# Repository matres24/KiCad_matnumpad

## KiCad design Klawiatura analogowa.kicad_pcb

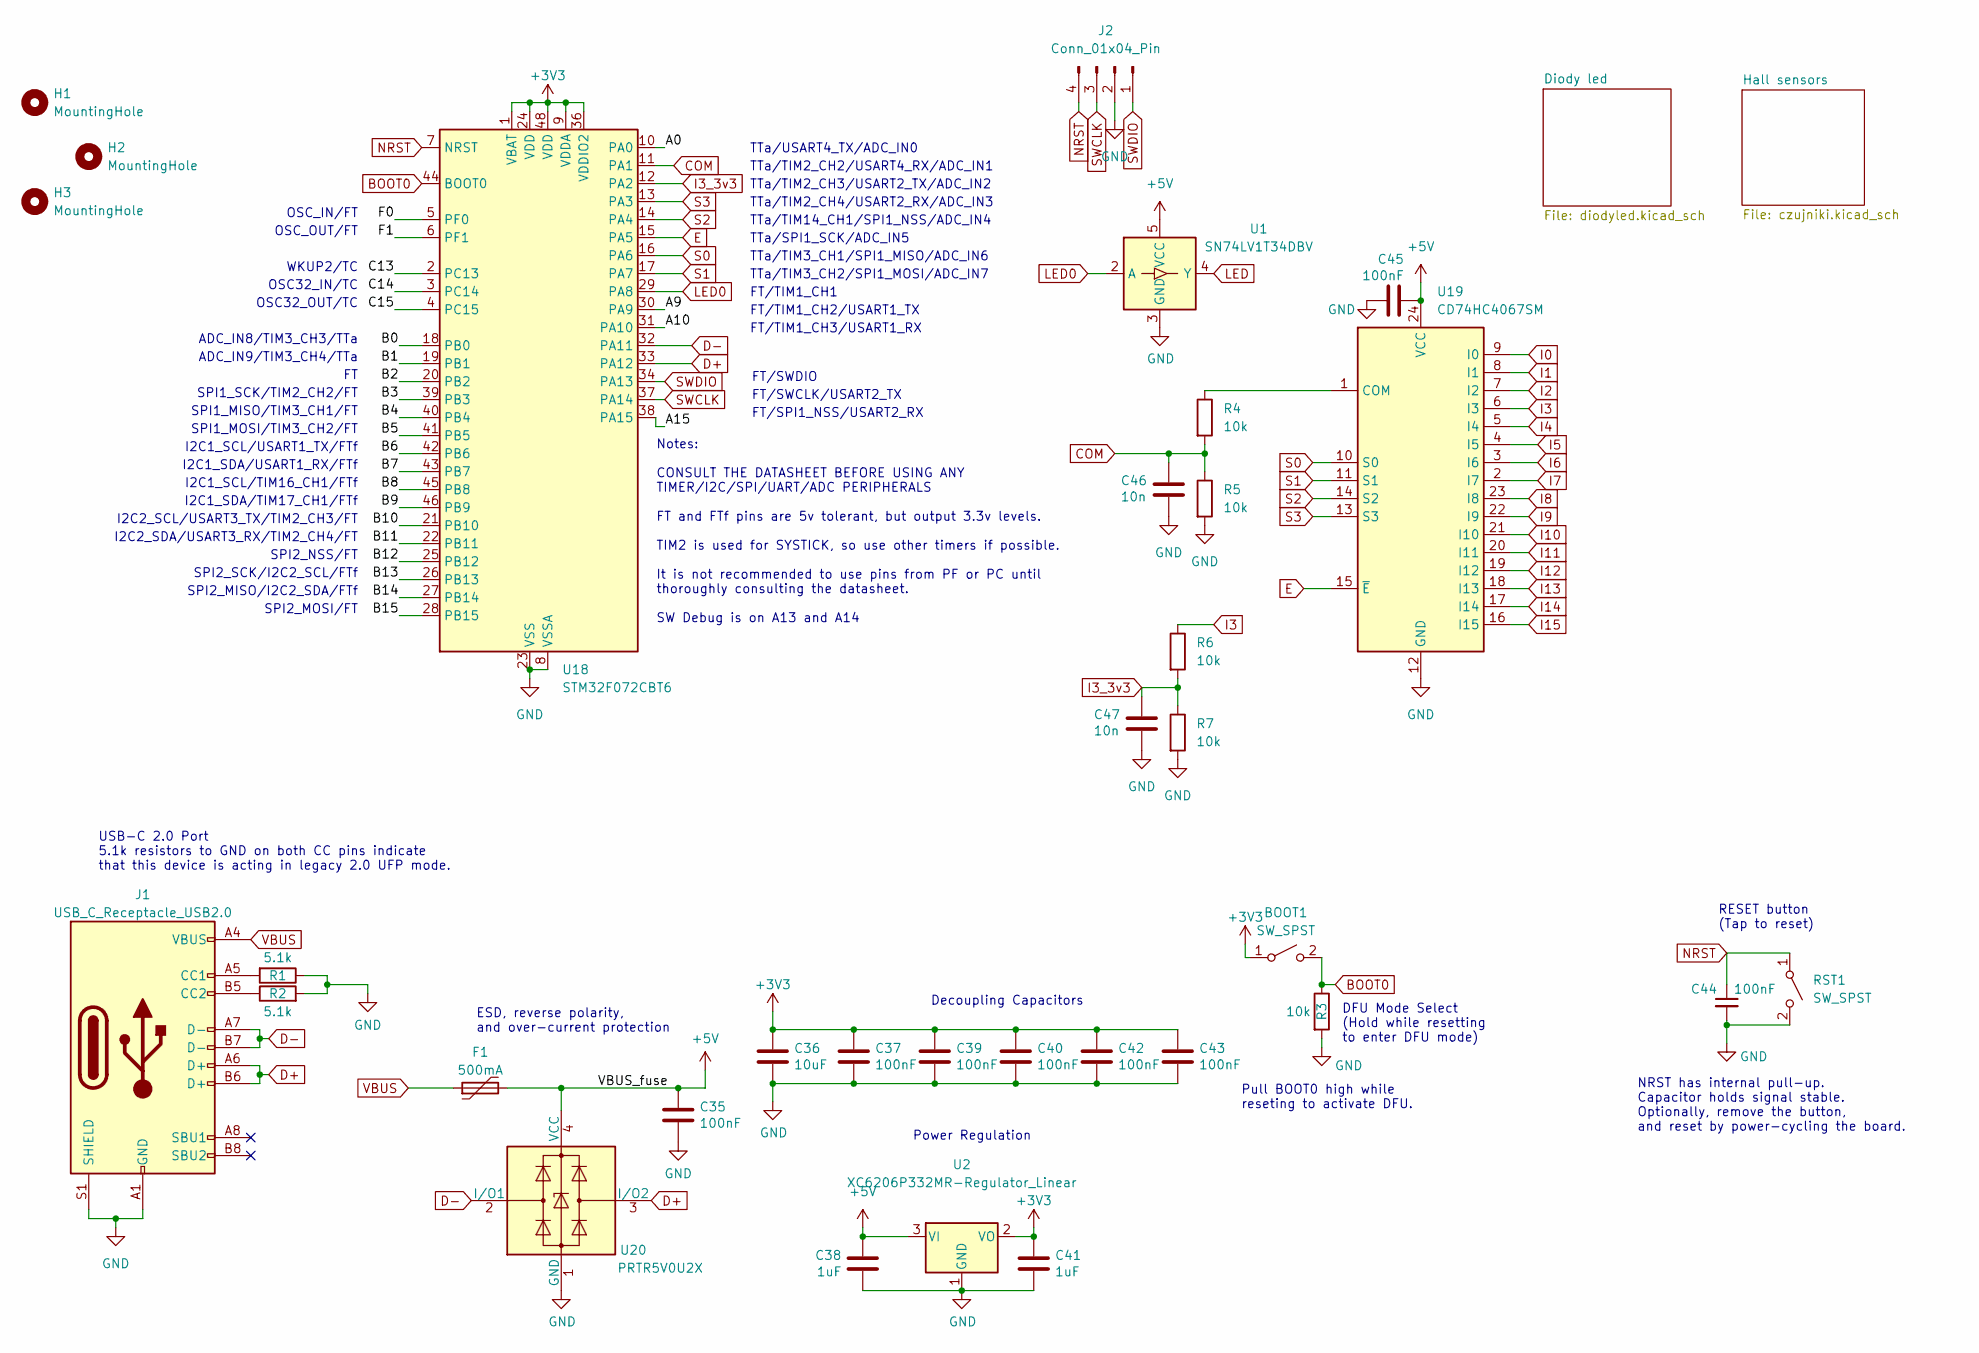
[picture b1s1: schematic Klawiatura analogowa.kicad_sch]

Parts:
BOOT1: SW_SPST; SW_SPST_B3U-1000P
C35, C37, C39, C40, C42, C43, C44, C45: 100nF; C_0402_1005Metric; LCSC C307331
C36: 10uF; C_0603_1608Metric; LCSC C307331
C38, C41: 1uF; C_0402_1005Metric; LCSC C307331
C46, C47: 10n; C_0402_1005Metric
F1: 500mA; Fuse_1206_3216Metric; LCSC C135341
H1, H2, H3: MountingHole; MountingHole_2.2mm_M2_ISO7380_Pad
J1: USB_C_Receptacle_USB2.0; USB_C_Receptacle_HRO_TYPE-C-31-M-12; JlcRotOffset 180
J2: Conn_01x04_Pin; PinHeader_1x04_P1.27mm_Vertical
R1, R2: 5.1k; R_0402_1005Metric
R3, R4, R5, R6, R7: 10k; R_0402_1005Metric
RST1: SW_SPST; SW_SPST_B3U-1000P
U1: SN74LV1T34DBV; SOT-23-5
U2: XC6206P332MR-Regulator_Linear; SOT-23; LCSC C5446
U18: STM32F072CBT6; LQFP-48_7x7mm_P0.5mm; JlcRotOffset 90
U19: CD74HC4067SM; SSOP-24_5.3x8.2mm_P0.65mm
U20: PRTR5V0U2X; SOT-143; LCSC C2827688

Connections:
+3V3: BOOT1.1 (A), C36.1, C37.1, C39.1, C40.1, C41.1, C42.1, C43.1, U2.2 (VO), U18.1 (VBAT), U18.9 (VDDA), U18.24 (VDD), U18.36 (VDDIO2), U18.48 (VDD)
+5V: C35.1, C38.1, C45.2, F1.2, U1.5 (VCC), U2.3 (VI), U19.24 (VCC), U20.4 (VCC); also elsewhere on the board
/A0: U18.10 (PA0)
/A9: U18.30 (PA9)
/A10: U18.31 (PA10)
/A15: U18.38 (PA15)
/B0: U18.18 (PB0)
/B1: U18.19 (PB1)
/B2: U18.20 (PB2)
/B3: U18.39 (PB3)
/B4: U18.40 (PB4)
/B5: U18.41 (PB5)
/B6: U18.42 (PB6)
/B7: U18.43 (PB7)
/B8: U18.45 (PB8)
/B9: U18.46 (PB9)
/B10: U18.21 (PB10)
/B11: U18.22 (PB11)
/B12: U18.25 (PB12)
/B13: U18.26 (PB13)
/B14: U18.27 (PB14)
/B15: U18.28 (PB15)
/C13: U18.2 (PC13)
/C14: U18.3 (PC14)
/C15: U18.4 (PC15)
/F0: U18.5 (PF0)
/F1: U18.6 (PF1)
BOOT0: BOOT1.2 (B), R3.1, U18.44 (BOOT0)
COM: C46.1, R4.2, R5.1, U18.11 (PA1)
D+: J1.A6 (D+), J1.B6 (D+), U18.33 (PA12), U20.3 (I/O2)
D-: J1.A7 (D-), J1.B7 (D-), U18.32 (PA11), U20.2 (I/O1)
E: U18.15 (PA5), U19.15 (~E)
GND: C35.2, C36.2, C37.2, C38.2, C39.2, C40.2, C41.2, C42.2, C43.2, C44.2, C45.1, C46.2, C47.2, J1.A1 (GND), J1.A12 (GND), J1.B1 (GND), J1.B12 (GND), J1.S1 (SHIELD), J2.2, R1.1, R2.2, R3.2, R5.2, R7.2, RST1.2 (B), U1.3 (GND), U2.1 (GND), U18.8 (VSSA), U18.23 (VSS), U18.35 (VSS), U18.47 (VSS), U19.12 (GND), U20.1 (GND); also elsewhere on the board
I0: U19.9 (I0); also elsewhere on the board
I1: U19.8 (I1); also elsewhere on the board
I2: U19.7 (I2); also elsewhere on the board
I3: R6.1, U19.6 (I3); also elsewhere on the board
I3_3v3: C47.1, R6.2, R7.1, U18.12 (PA2)
I4: U19.5 (I4); also elsewhere on the board
I5: U19.4 (I5); also elsewhere on the board
I6: U19.3 (I6); also elsewhere on the board
I7: U19.2 (I7); also elsewhere on the board
I8: U19.23 (I8); also elsewhere on the board
I9: U19.22 (I9); also elsewhere on the board
I10: U19.21 (I10); also elsewhere on the board
I11: U19.20 (I11); also elsewhere on the board
I12: U19.19 (I12); also elsewhere on the board
I13: U19.18 (I13); also elsewhere on the board
I14: U19.17 (I14); also elsewhere on the board
I15: U19.16 (I15); also elsewhere on the board
LED: U1.4 (Y); also elsewhere on the board
LED0: U1.2 (A), U18.29 (PA8)
NRST: C44.1, J2.4, RST1.1 (A), U18.7 (NRST)
unnamed: J1.A5 (CC1), R1.2
unnamed: J1.B5 (CC2), R2.1
unnamed: R4.1, U19.1 (COM)
S0: U18.16 (PA6), U19.10 (S0)
S1: U18.17 (PA7), U19.11 (S1)
S2: U18.14 (PA4), U19.14 (S2)
S3: U18.13 (PA3), U19.13 (S3)
SWCLK: J2.3, U18.37 (PA14)
SWDIO: J2.1, U18.34 (PA13)
VBUS: F1.1, J1.A4 (VBUS), J1.A9 (VBUS), J1.B4 (VBUS), J1.B9 (VBUS)

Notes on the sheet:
SPI1_MISO/TIM3_CH1/FT
SPI2_MISO/I2C2_SDA/FTf
Notes: CONSULT THE DATASHEET BEFORE USING ANY TIMER/I2C/SPI/UART/ADC PERIPHERALS FT and FTf pins are 5v tolerant, but output 3.3v levels. TIM2 is used for SYSTICK, so use other timers if possible. It is not recommended to use pins from PF or PC until thoroughly consulting the datasheet. SW Debug is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
I2C2_SDA/USART3_RX/TIM2_CH4/FT
ESD, reverse polarity, and over-current protection
I2C1_SDA/USART1_RX/FTf
OSC_OUT/FT
USB-C 2.0 Port 5.1k resistors to GND on both CC pins indicate that this device is acting in legacy 2.0 UFP mode.
DFU Mode Select (Hold while resetting to enter DFU mode)
FT/SWDIO
TTa/TIM3_CH1/SPI1_MISO/ADC_IN6
TTa/SPI1_SCK/ADC_IN5
TTa/TIM2_CH3/USART2_TX/ADC_IN2
TTa/TIM3_CH2/SPI1_MOSI/ADC_IN7
SPI2_SCK/I2C2_SCL/FTf
ADC_IN8/TIM3_CH3/TTa
ADC_IN9/TIM3_CH4/TTa
OSC32_OUT/TC
SPI2_NSS/FT
Power Regulation
I2C2_SCL/USART3_TX/TIM2_CH3/FT
SPI2_MOSI/FT
RESET button (Tap to reset)
TTa/TIM14_CH1/SPI1_NSS/ADC_IN4
FT/TIM1_CH1
I2C1_SDA/TIM17_CH1/FTf
SPI1_MOSI/TIM3_CH2/FT
TTa/TIM2_CH4/USART2_RX/ADC_IN3
I2C1_SCL/TIM16_CH1/FTf
OSC32_IN/TC
WKUP2/TC
FT/TIM1_CH3/USART1_RX
NRST has internal pull-up. Capacitor holds signal stable. Optionally, remove the button, and reset by power-cycling the board.
FT/SPI1_NSS/USART2_RX
I2C1_SCL/USART1_TX/FTf
FT/SWCLK/USART2_TX
OSC_IN/FT
Pull BOOT0 high while reseting to activate DFU.
Decoupling Capacitors
TTa/USART4_TX/ADC_IN0

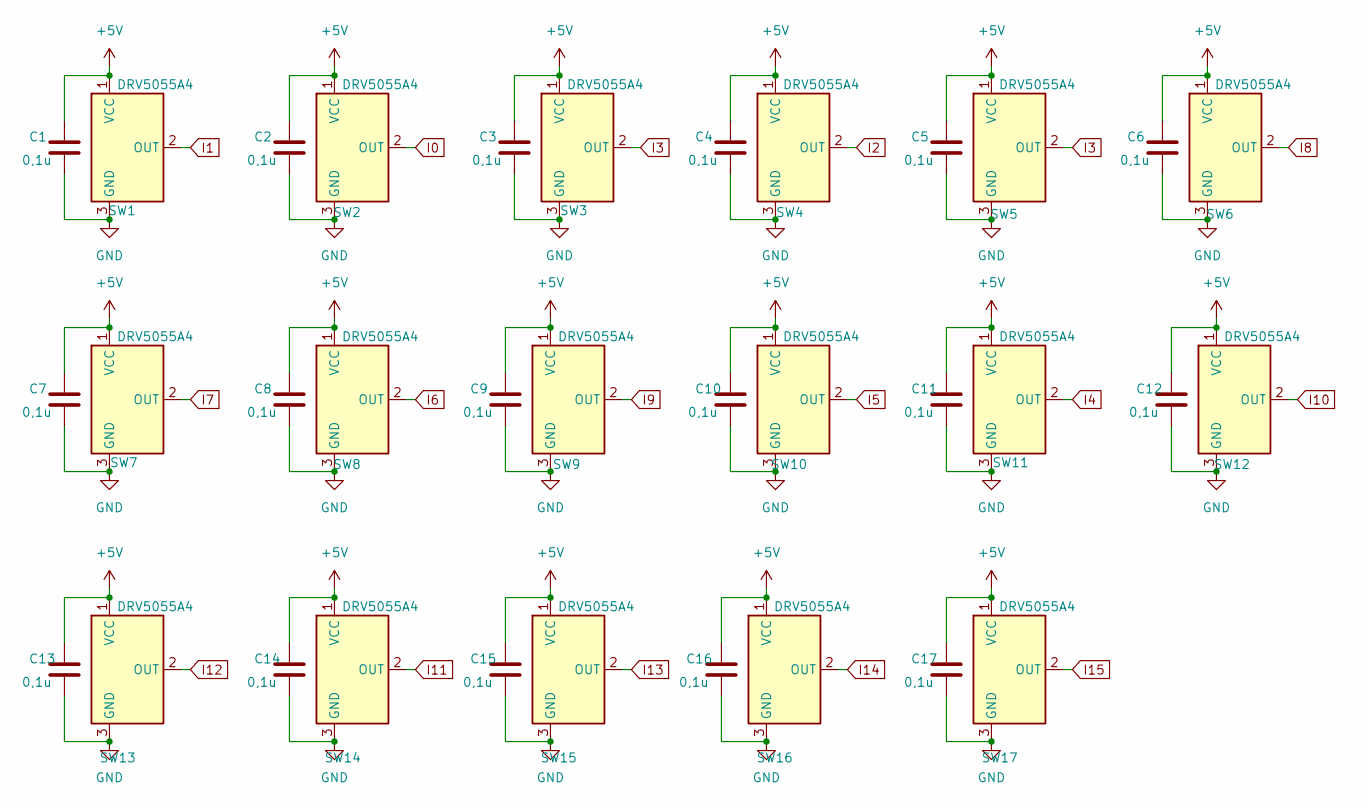
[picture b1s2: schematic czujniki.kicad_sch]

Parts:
C1, C2, C3, C4, C5, C6, C7, C8, C9, C10, C11, C12, C13, C14, C15, C16, C17: 0,1u; C_0402_1005Metric
SW1, SW2, SW3, SW4, SW5, SW6, SW7, SW8, SW9, SW10, SW11, SW12, SW14, SW17: DRV5055A4; MX-Analog-1U
SW13: DRV5055A4; MX-Analog-2U
SW15, SW16: DRV5055A4; MX-Analog-2U-Vertical-ReversedStabilizers

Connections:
+5V: C1.1, C2.1, C3.1, C4.1, C5.1, C6.1, C7.1, C8.1, C9.1, C10.1, C11.1, C12.1, C13.1, C14.1, C15.1, C16.1, C17.1, SW1.1 (VCC), SW2.1 (VCC), SW3.1 (VCC), SW4.1 (VCC), SW5.1 (VCC), SW6.1 (VCC), SW7.1 (VCC), SW8.1 (VCC), SW9.1 (VCC), SW10.1 (VCC), SW11.1 (VCC), SW12.1 (VCC), SW13.1 (VCC), SW14.1 (VCC), SW15.1 (VCC), SW16.1 (VCC), SW17.1 (VCC); also elsewhere on the board
GND: C1.2, C2.2, C3.2, C4.2, C5.2, C6.2, C7.2, C8.2, C9.2, C10.2, C11.2, C12.2, C13.2, C14.2, C15.2, C16.2, C17.2, SW1.3 (GND), SW2.3 (GND), SW3.3 (GND), SW4.3 (GND), SW5.3 (GND), SW6.3 (GND), SW7.3 (GND), SW8.3 (GND), SW9.3 (GND), SW10.3 (GND), SW11.3 (GND), SW12.3 (GND), SW13.3 (GND), SW14.3 (GND), SW15.3 (GND), SW16.3 (GND), SW17.3 (GND); also elsewhere on the board
I0: SW2.2 (OUT); also elsewhere on the board
I1: SW1.2 (OUT); also elsewhere on the board
I2: SW4.2 (OUT); also elsewhere on the board
I3: SW3.2 (OUT), SW5.2 (OUT); also elsewhere on the board
I4: SW11.2 (OUT); also elsewhere on the board
I5: SW10.2 (OUT); also elsewhere on the board
I6: SW8.2 (OUT); also elsewhere on the board
I7: SW7.2 (OUT); also elsewhere on the board
I8: SW6.2 (OUT); also elsewhere on the board
I9: SW9.2 (OUT); also elsewhere on the board
I10: SW12.2 (OUT); also elsewhere on the board
I11: SW14.2 (OUT); also elsewhere on the board
I12: SW13.2 (OUT); also elsewhere on the board
I13: SW15.2 (OUT); also elsewhere on the board
I14: SW16.2 (OUT); also elsewhere on the board
I15: SW17.2 (OUT); also elsewhere on the board

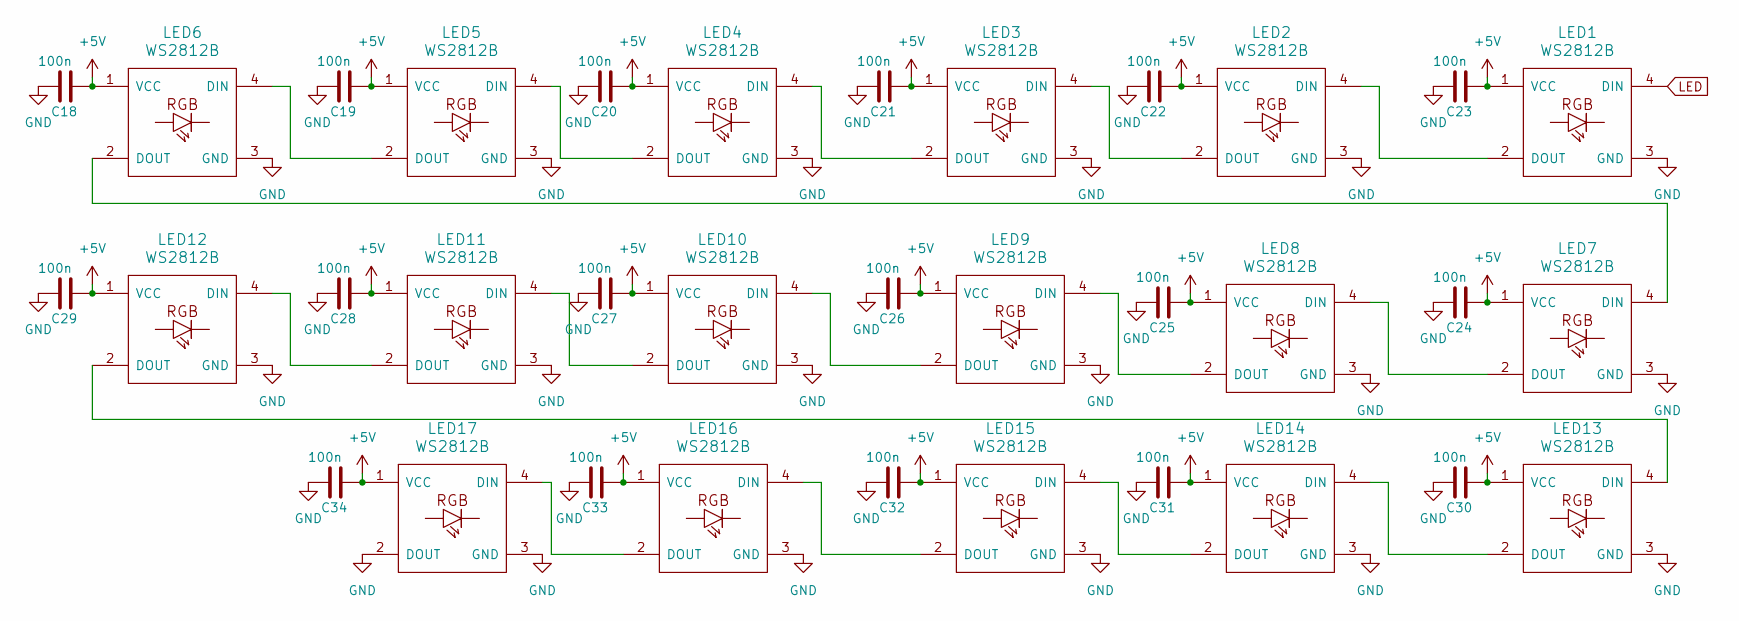
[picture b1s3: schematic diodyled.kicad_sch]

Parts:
C18, C19, C20, C21, C22, C23, C24, C25, C26, C27, C28, C29, C30, C31, C32, C33, C34: 100n; C_0402_1005Metric
LED1, LED2, LED3, LED4, LED5, LED6, LED7, LED8, LED9, LED10, LED11, LED12, LED13, LED14, LED15, LED16, LED17: WS2812B; MX-LED_WS2812B_wide

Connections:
+5V: C18.2, C19.2, C20.2, C21.2, C22.2, C23.2, C24.2, C25.2, C26.2, C27.2, C28.2, C29.2, C30.2, C31.2, C32.2, C33.2, C34.2, LED1.1 (VCC), LED2.1 (VCC), LED3.1 (VCC), LED4.1 (VCC), LED5.1 (VCC), LED6.1 (VCC), LED7.1 (VCC), LED8.1 (VCC), LED9.1 (VCC), LED10.1 (VCC), LED11.1 (VCC), LED12.1 (VCC), LED13.1 (VCC), LED14.1 (VCC), LED15.1 (VCC), LED16.1 (VCC), LED17.1 (VCC); also elsewhere on the board
GND: C18.1, C19.1, C20.1, C21.1, C22.1, C23.1, C24.1, C25.1, C26.1, C27.1, C28.1, C29.1, C30.1, C31.1, C32.1, C33.1, C34.1, LED1.3 (GND), LED2.3 (GND), LED3.3 (GND), LED4.3 (GND), LED5.3 (GND), LED6.3 (GND), LED7.3 (GND), LED8.3 (GND), LED9.3 (GND), LED10.3 (GND), LED11.3 (GND), LED12.3 (GND), LED13.3 (GND), LED14.3 (GND), LED15.3 (GND), LED16.3 (GND), LED17.2 (DOUT), LED17.3 (GND); also elsewhere on the board
LED: LED1.4 (DIN); also elsewhere on the board
unnamed: LED1.2 (DOUT), LED2.4 (DIN)
unnamed: LED2.2 (DOUT), LED3.4 (DIN)
unnamed: LED3.2 (DOUT), LED4.4 (DIN)
unnamed: LED4.2 (DOUT), LED5.4 (DIN)
unnamed: LED5.2 (DOUT), LED6.4 (DIN)
unnamed: LED6.2 (DOUT), LED7.4 (DIN)
unnamed: LED7.2 (DOUT), LED8.4 (DIN)
unnamed: LED8.2 (DOUT), LED9.4 (DIN)
unnamed: LED9.2 (DOUT), LED10.4 (DIN)
unnamed: LED10.2 (DOUT), LED11.4 (DIN)
unnamed: LED11.2 (DOUT), LED12.4 (DIN)
unnamed: LED12.2 (DOUT), LED13.4 (DIN)
unnamed: LED13.2 (DOUT), LED14.4 (DIN)
unnamed: LED14.2 (DOUT), LED15.4 (DIN)
unnamed: LED15.2 (DOUT), LED16.4 (DIN)
unnamed: LED16.2 (DOUT), LED17.4 (DIN)

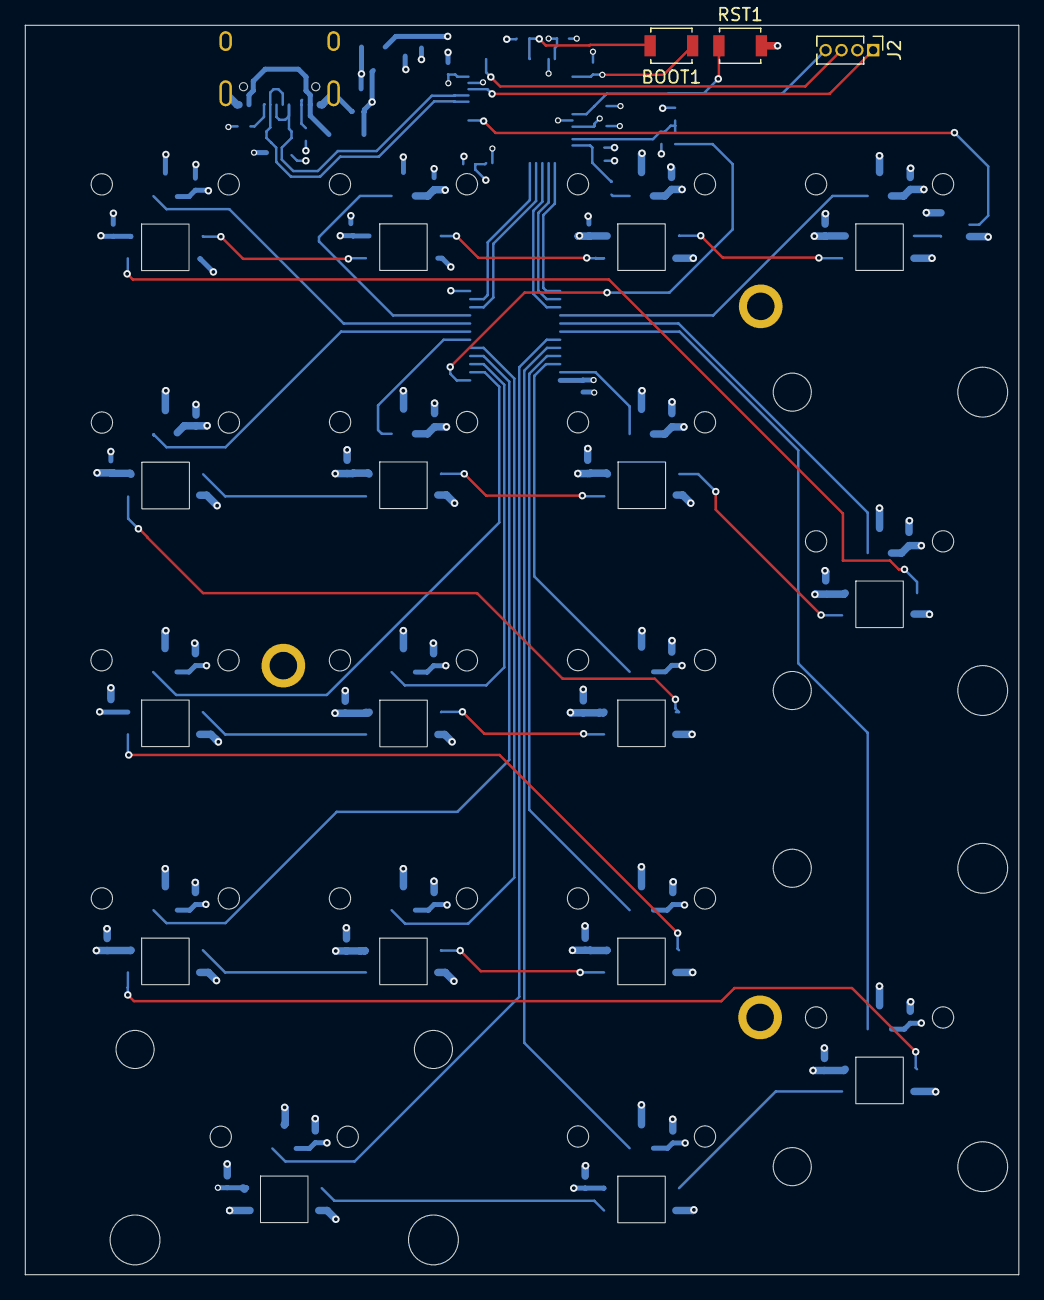
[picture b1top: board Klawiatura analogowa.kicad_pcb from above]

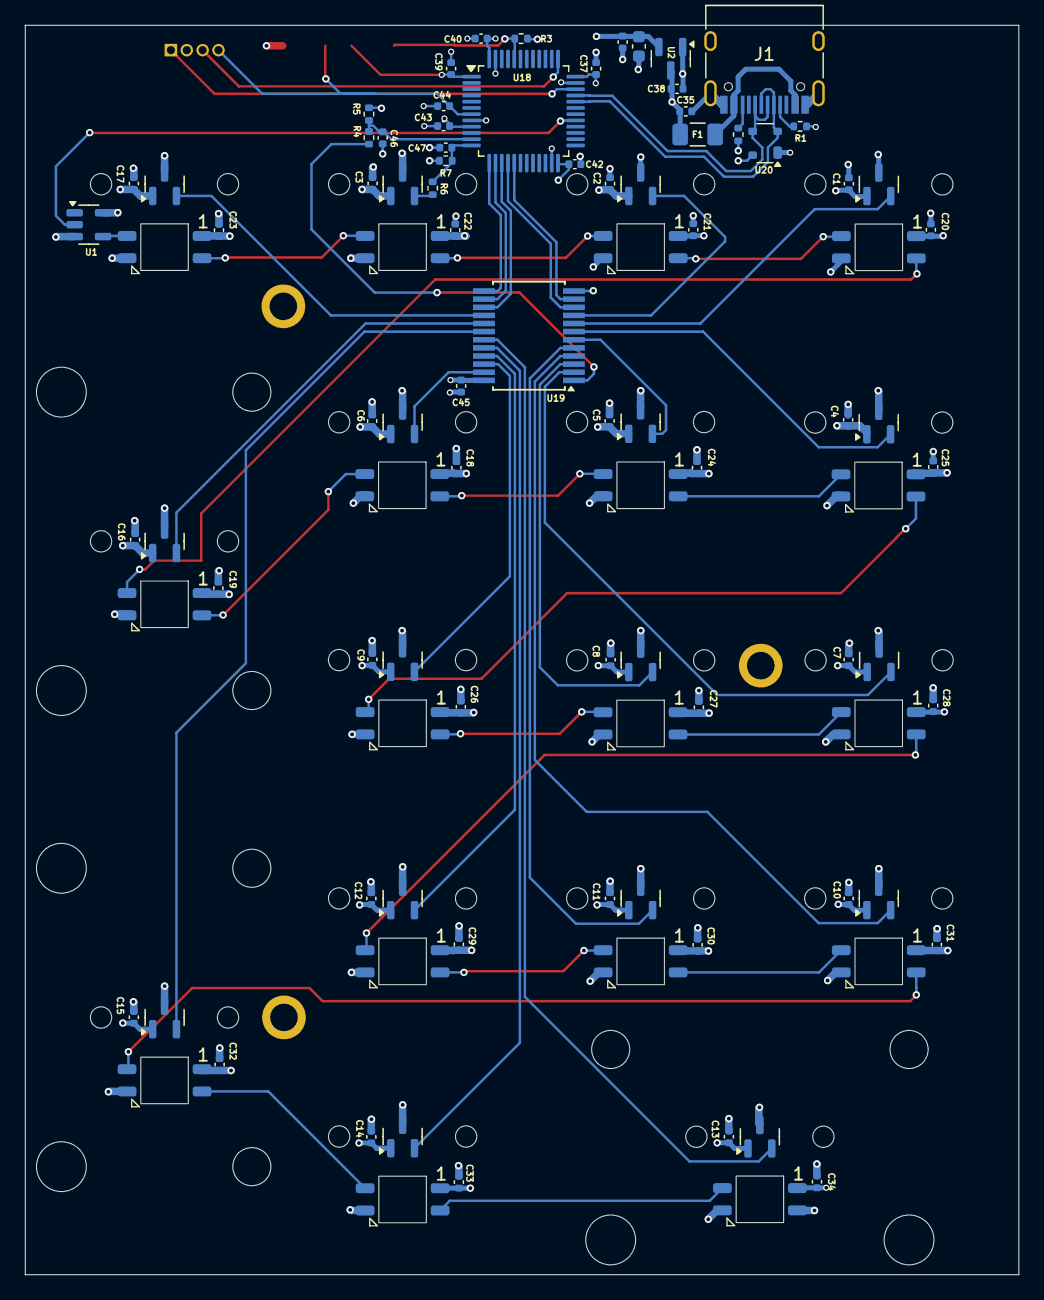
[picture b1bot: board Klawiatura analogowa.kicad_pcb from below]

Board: 4 copper layers, 79.5 x 100.0 mm, 101 parts (61 on the bottom side), 54 nets.

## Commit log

2024-12-07 Full production files for HE PCB
2024-12-08 Poprawiono wygląd schematu
